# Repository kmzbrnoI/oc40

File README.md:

Universal optocoupler module OC-40
==================================

Module with 4 optocouplers.

Designed in KiCad 9 by Jan Malina.

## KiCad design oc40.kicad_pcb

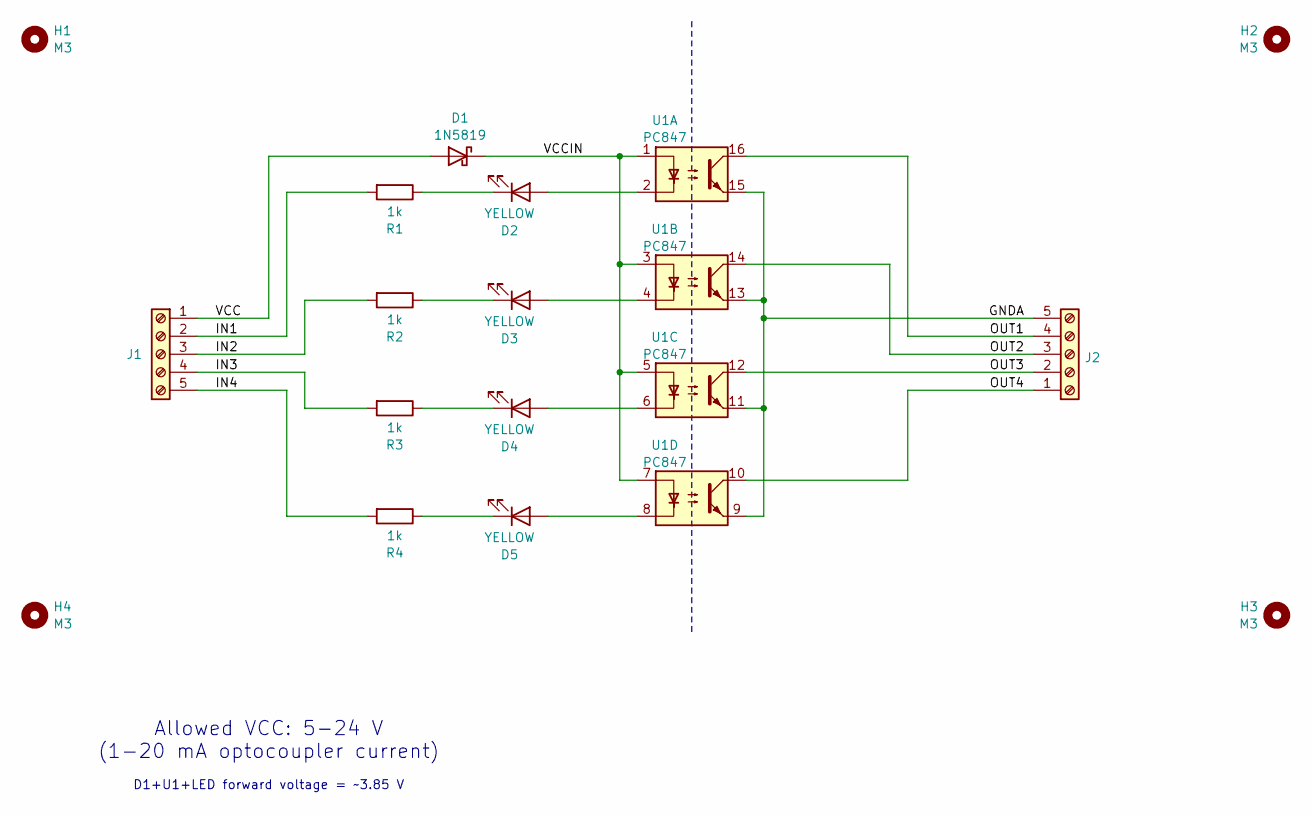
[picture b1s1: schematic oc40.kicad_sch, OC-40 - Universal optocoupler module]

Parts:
D1: 1N5819; D_SOD-123
D2, D3, D4, D5: YELLOW; LED_0805_2012Metric_Pad1.15x1.40mm_HandSolder
H1, H2, H3, H4: M3; MountingHole_3.2mm_M3_Pad_Via
J1, J2: TerminalBlock_4Ucon_1x05_P3.50mm_Horizontal
R1, R2, R3, R4: 1k; R_0805_2012Metric_Pad1.20x1.40mm_HandSolder
U1: PC847; DIP-16_W7.62mm_LongPads

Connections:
/GNDA: J2.5, U1.9, U1.11, U1.13, U1.15
/IN1: J1.2, R1.2
/IN2: J1.3, R2.2
/IN3: J1.4, R3.2
/IN4: J1.5, R4.2
/OUT1: J2.4, U1.16
/OUT2: J2.3, U1.14
/OUT3: J2.2, U1.12
/OUT4: J2.1, U1.10
/VCC: D1.2 (A), J1.1
/VCCIN: D1.1 (K), U1.1, U1.3, U1.5, U1.7
unnamed: D2.2 (A), U1.2
unnamed: D2.1 (K), R1.1
unnamed: D3.2 (A), U1.4
unnamed: D3.1 (K), R2.1
unnamed: D4.2 (A), U1.6
unnamed: D4.1 (K), R3.1
unnamed: D5.2 (A), U1.8
unnamed: D5.1 (K), R4.1

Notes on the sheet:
D1+U1+LED forward voltage = ~3.85 V
Allowed VCC: 5-24 V (1-20 mA optocoupler current)

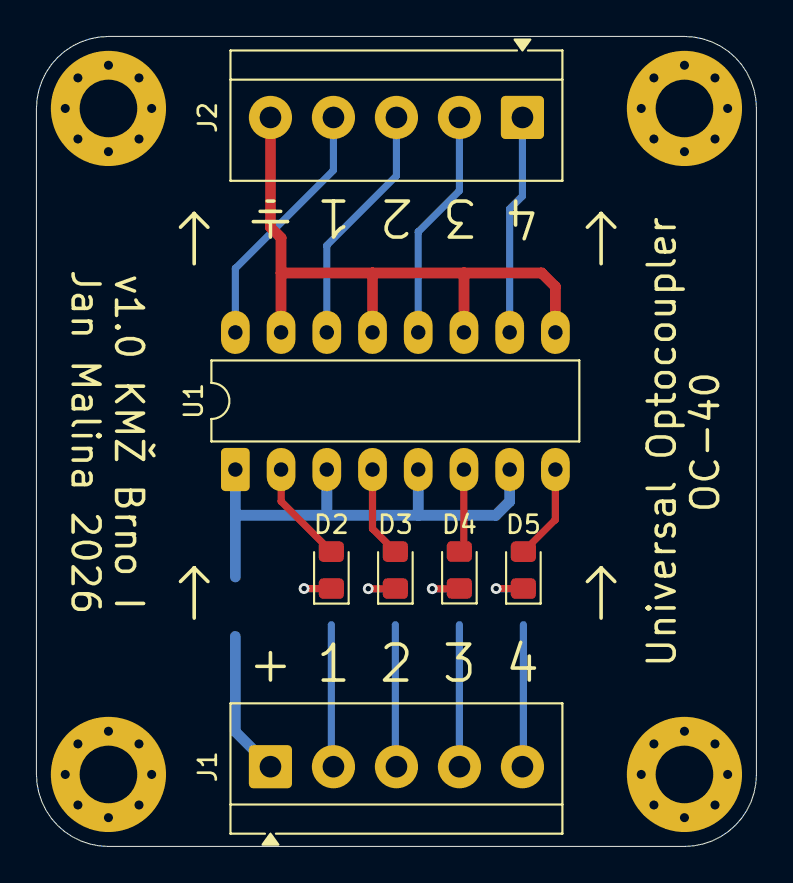
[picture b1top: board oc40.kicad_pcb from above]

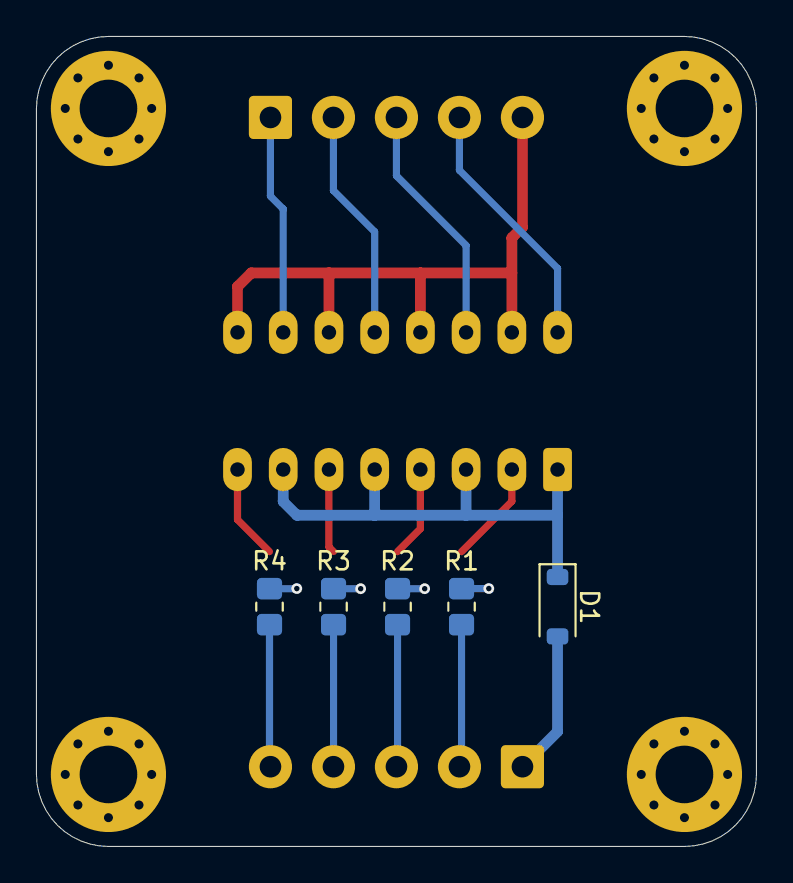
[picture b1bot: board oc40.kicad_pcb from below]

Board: 2 copper layers, 40.0 x 45.0 mm, 16 parts (5 on the bottom side), 19 nets.

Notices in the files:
oc40.kicad_sch:
https://creativecommons.org/licenses/by-sa/4.0
Released under the Creative Commons Attribution-ShareAlike 4.0 License
